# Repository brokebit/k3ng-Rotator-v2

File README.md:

# K3NG Rotator Controller

# LCD2004 Connection
**LCD Pin -> Rotator Pin**
1. 1 (GND) -> GND
2. 2 (VCC) -> +5V
3. 3 (Contrast) -> Center Pin (2) of Contrast Potentiometer
4. 4 (Register Select) -> LCD_RST
5. 5 (Read/Write) -> GND
6. 6 (Enable) -> LCD_EN
7. 7 (Data 0) -> NC
8. 8 (Data 1) -> NC
9. 9 (Data 2) -> NC
10. 10 (Data 3) -> NC
11. 11 (Data 4) -> LCD_D4
12. 12 (Data 5) -> LCD_D5
13. 13 (Data 6) -> LCD_D6
14. 14 (Data 7) -> LCD_D7
15. 15 (Backlight +) -> +5V + Contrast Potentiometer Pin 1
16. 16 (Backlight -) -> GND + Contrast Potentiometer Pin 3

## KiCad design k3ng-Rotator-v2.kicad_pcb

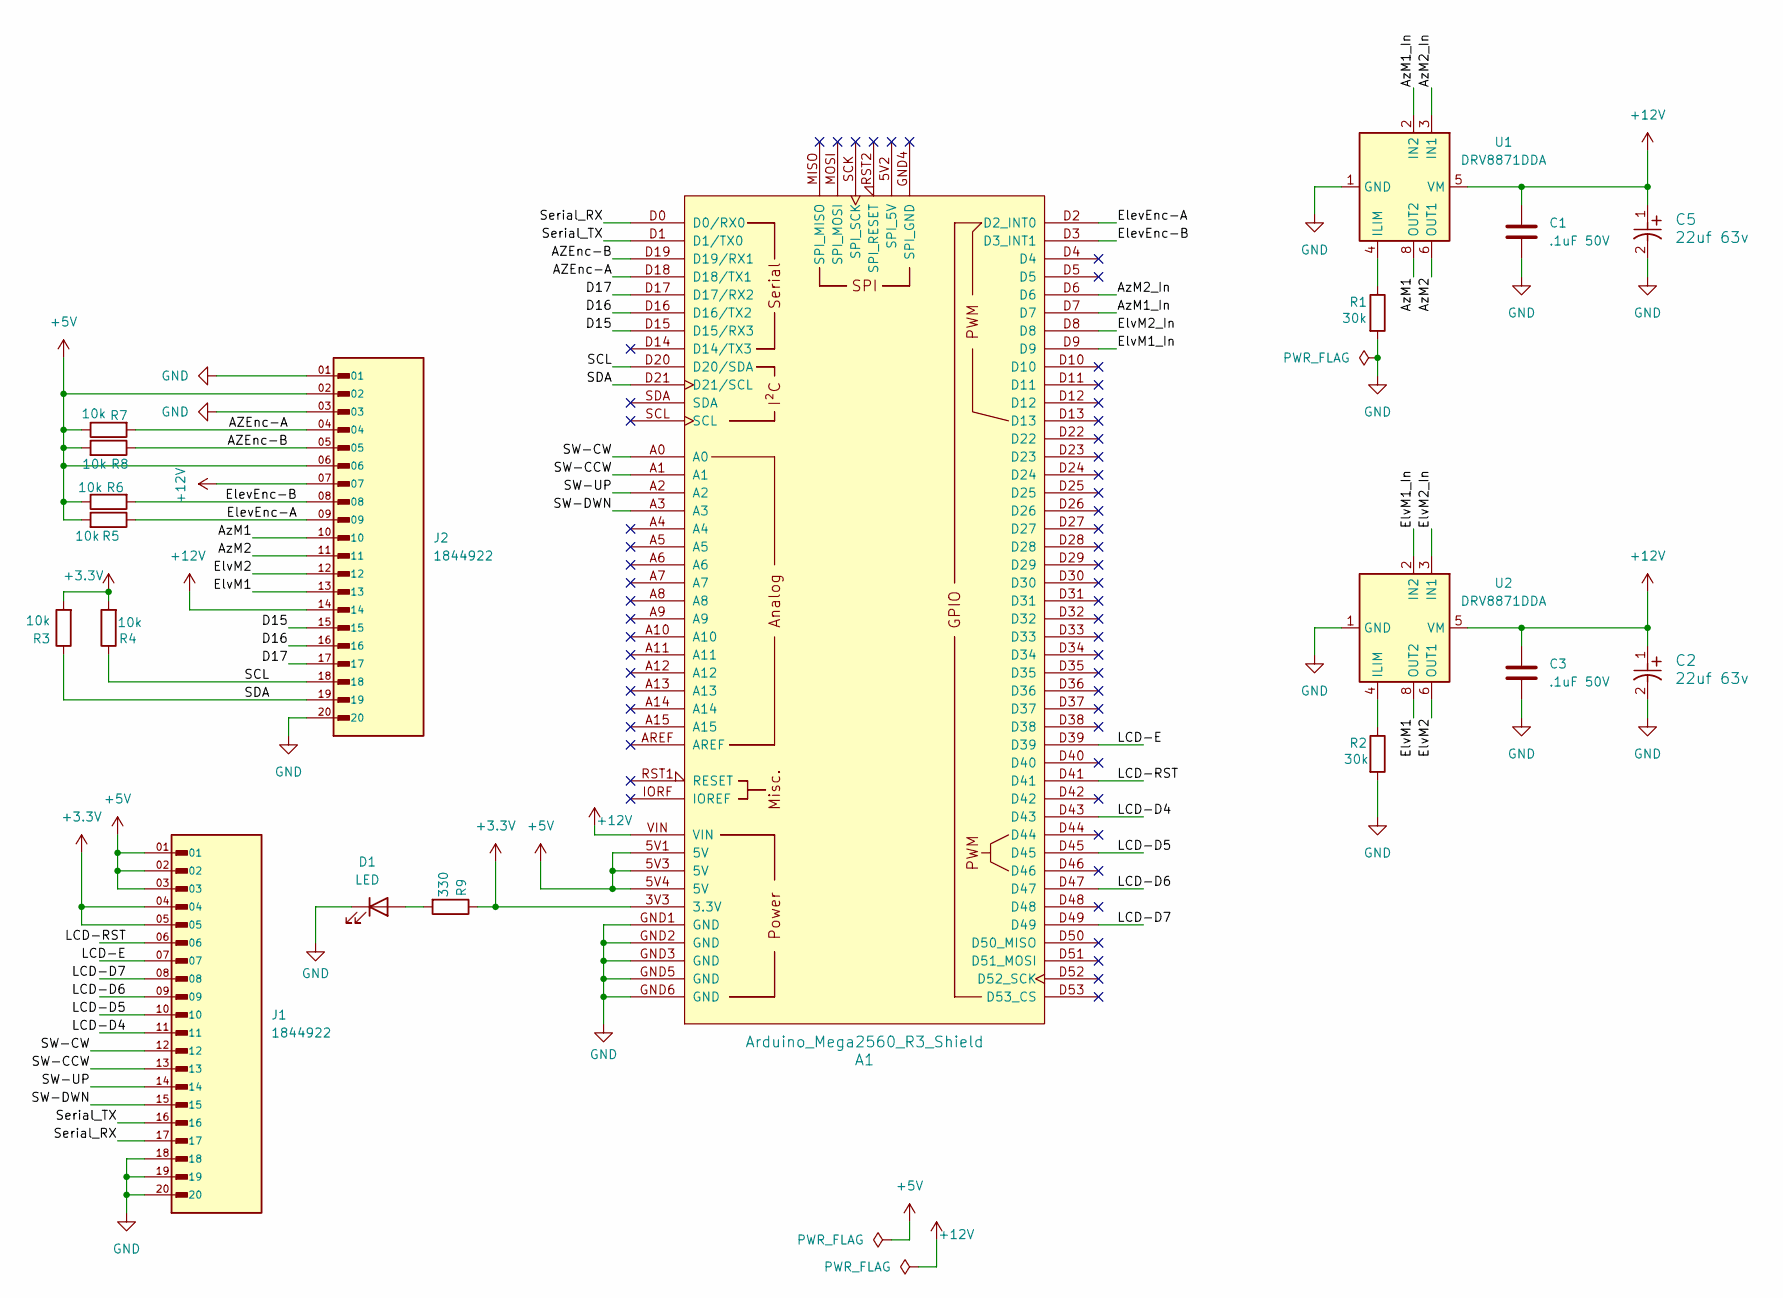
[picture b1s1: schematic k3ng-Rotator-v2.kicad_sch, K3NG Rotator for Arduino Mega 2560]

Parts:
A1: Arduino_Mega2560_R3_Shield
C1, C3: .1uF 50V; C_1206_3216Metric
C2, C5: 22uf 63v; PCAP_EEHZ_D8_PAN
D1: LED; LED_1206_3216Metric
J1, J2: 1844922; PHOENIX_1844922; PARTREV 25.02.2015
R1, R2: 30k; R_1206_3216Metric
R3, R4, R5, R6, R7, R8: 10k; R_1206_3216Metric
R9: 330; R_1206_3216Metric
U1, U2: DRV8871DDA; Texas_HTSOP-8-1EP_3.9x4.9mm_P1.27mm_EP2.95x4.9mm_Mask2.4x3.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

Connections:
+3.3V: A1.3V3 (3.3V), J1.04, J1.05, R3.2, R4.2, R9.1
+5V: A1.5V1 (5V), A1.5V3 (5V), A1.5V4 (5V), J1.01, J1.02, J1.03, J2.02, J2.06, R5.2, R6.1, R7.1, R8.2
+12V: A1.VIN, C1.1, C2.1, C3.1, C5.1, J2.07, J2.14, U1.5 (VM), U2.5 (VM)
/AZEnc-A: A1.D18 (D18/TX1), J2.04, R7.2
/AZEnc-B: A1.D19 (D19/RX1), J2.05, R8.1
/AzM1: J2.10, U1.8 (OUT2)
/AzM1_In: A1.D7, U1.2 (IN2)
/AzM2: J2.11, U1.6 (OUT1)
/AzM2_In: A1.D6, U1.3 (IN1)
/D15: A1.D15 (D15/RX3), J2.15
/D16: A1.D16 (D16/TX2), J2.16
/D17: A1.D17 (D17/RX2), J2.17
/ElevEnc-A: A1.D2 (D2_INT0), J2.09, R5.1
/ElevEnc-B: A1.D3 (D3_INT1), J2.08, R6.2
/ElvM1: J2.13, U2.8 (OUT2)
/ElvM1_In: A1.D9, U2.2 (IN2)
/ElvM2: J2.12, U2.6 (OUT1)
/ElvM2_In: A1.D8, U2.3 (IN1)
/LCD-D4: A1.D43, J1.11
/LCD-D5: A1.D45, J1.10
/LCD-D6: A1.D47, J1.09
/LCD-D7: A1.D49, J1.08
/LCD-E: A1.D39, J1.07
/LCD-RST: A1.D41, J1.06
/SCL: A1.D20 (D20/SDA), J2.18, R4.1
/SDA: A1.D21 (D21/SCL), J2.19, R3.1
/SW-CCW: A1.A1, J1.13
/SW-CW: A1.A0, J1.12
/SW-DWN: A1.A3, J1.15
/SW-UP: A1.A2, J1.14
/Serial_RX: A1.D0 (D0/RX0), J1.17
/Serial_TX: A1.D1 (D1/TX0), J1.16
GND: A1.GND1 (GND), A1.GND2 (GND), A1.GND3 (GND), A1.GND5 (GND), A1.GND6 (GND), C1.2, C2.2, C3.2, C5.2, D1.1 (K), J1.18, J1.19, J1.20, J2.01, J2.03, J2.20, R1.2, R2.2, U1.1 (GND), U1.7 (GND), U1.9 (GND), U2.1 (GND), U2.7 (GND), U2.9 (GND)
unnamed: D1.2 (A), R9.2
unnamed: R1.1, U1.4 (ILIM)
unnamed: R2.1, U2.4 (ILIM)

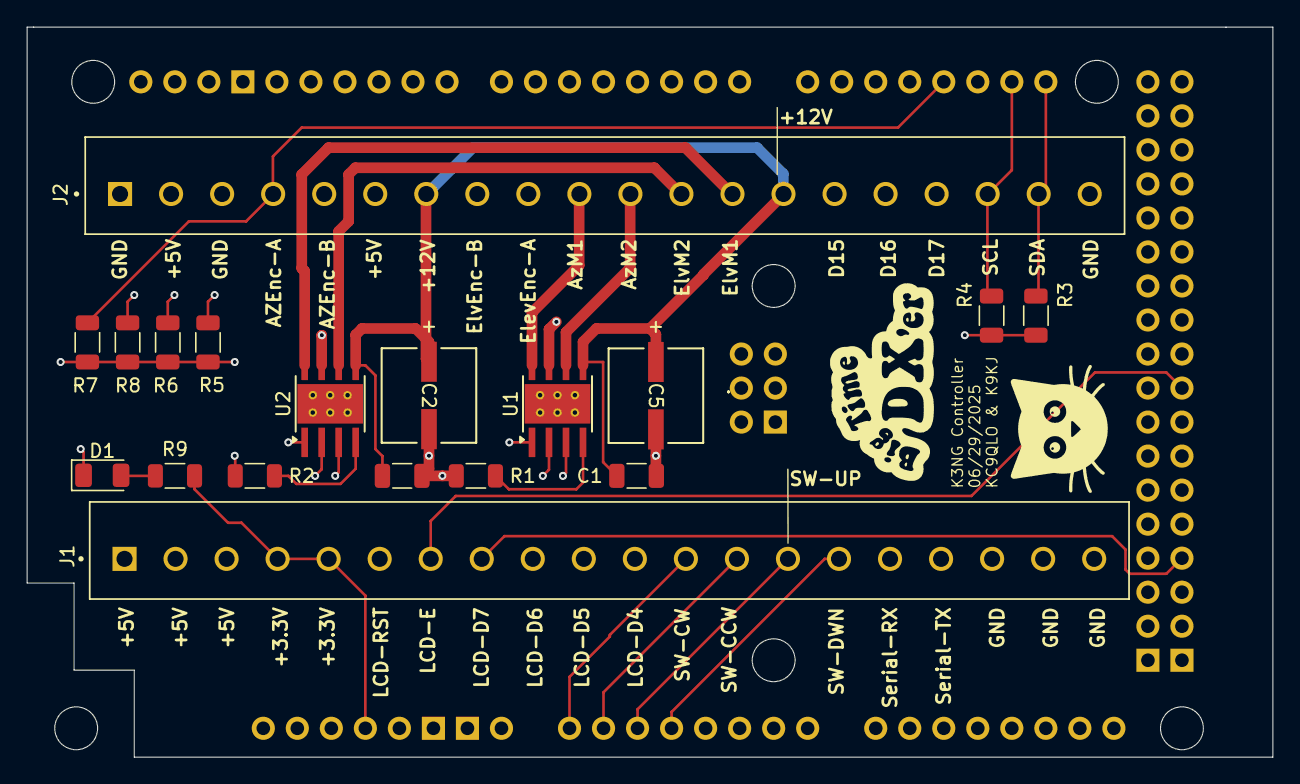
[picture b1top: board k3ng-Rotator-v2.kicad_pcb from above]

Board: 6 copper layers, 93.0 x 54.5 mm, 19 parts (0 on the bottom side), 36 nets.

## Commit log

2025-06-30 Test
2025-06-30 Maybe this will work
2025-07-10 Fix silkscreen, add drawing and step file and dxf for stencil
